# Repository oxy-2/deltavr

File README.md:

# DeltaVR

DeltaVR is a open-source headset with its own controllers made for pcvr, with smaller optics than normal fresnels, custom pcbs and 2 cameras for slam tracking

### our headset:

### our pcbs:

Being a tiny bit more technical I and after the first hundred hours i did alone my 2 friends worked on making an open-source, lightweight PCVR headset built  to be a step up from the hadesvr headset while being more oriented towards technical users due to the smd components, it uses almost all custom hardware aside from the microcontroller, cameras, lenses, screens and drivers, and like linear rods ig, other than that everything is made by us with customs pcbs, and a almost entirely 3d printable design aside from again the ⌀5mm x 160mm stainless steel linear rods, the overarching goal of deltavr was an advanced opensource VR headset with large ipd accommodation, with inside out SLAM tracking and constellation tracked controllers with actually analog triggers on our custom controllers, all under 500 if you have the tools (we got all the way down to 390 actually!)

Oh also in the repo if you wanna see like logs we wrote for every week of the project while in thirdspace then check the /obsidianfiles/ directory, it has all the week folders and hopefully lol well written logs made by all of us with no AI for writing cuz its a tool and that would be stinky.

Also heres the Youtube video we made abt the project <3
https://youtu.be/ISufVPaX-EE

---

## Table of Contents

- [Features](##features)
    
- [Hardware Overview](##hardware-overview)
    
    - [Headset](###headset)
        
    - [Controllers](###controllers)
        
    - [Optics](###optics)
        
    - [Communication](###communication)
        
    - [PCBs](###PCBs)
        
- [Design Decisions](##design-decisions)
	
	- [Cameras](###Cameras)
		
	- [Wireless Communication](###Communication-Wireless)
	    
	- [Optical System](###Optical-System)
		
	- [Mechanical Design](###Mechanical-Design)
	    
- [Firmware](##firmware)
    
- [Assembly](##assembly)
    
- [Bill of Materials](##bill-of-materials)
    
- [Development Status](##development-status)
    
- [Known Issues](##known-issues)
    
- [Project Links](##project-links)
    
- [Credits](##credits)
    
- [License](##license)

---

## Features

- 2x OV9281 global shutter cameras at 120 fps, combined by a usb hub with the hmd pcb all into one 3.2 gen 2 cable to your pc

- custom hmd pcb, mostly smd (hence the technical users bit)

- pseudo pancake optics with 2x fresnels per eye giving better dimensions for just 20 euros for all 4 of the lenses

- a big ipd range, accommodating for all possible human ipd ranges that aren't legit 1 in a trillion

- made to be printed with asa from my own modified ender 3 so like hopefully anyone can print as long as u have an enclosure for the printer, the cushions also are just tpu-lw

- steamvr pcvr compatible

- custom controllers as a part of the project unlike other projects with 3rd party controllers

- high quality imus and mcus, LSM6DSV16Xs and nRF52840s respectively

- tmr joysticks so they never drift and use less battery

- 2 hall effect triggers with an actual analog range for inputs 

- ir constellation tracked controllers

- NRF24L01 on nordic's esb protocol for good range and battery also u.fl support if you want

- under 500 euros if you own the tools, we got all the way down to 390 euros

> *note: deltavr is still and will for a while still be in development, some of these features aren't ready but all listed are being worked on, also in the future there could be more features.

---

## Hardware-Overview

DeltaVR is a custom designed headset with a pair of also custom controllers, its a combination of commercially available components with custom pcbs and mostly 3d printed mechanical parts.

---
### Headset

The headset uses 2x OV9281 global shutter cameras at 120fps for SLAM tracking and tracking.

The cameras and main hmd pcb all connect back to the headset over a usb 3.2 gen 2 hub or if u want ig u can connect them just by 3 cables.

Each of the controllers and the headset pcb have have their own LSM6DSV16X imu and a nRF24L01 gt-24 smd radio module.

The mechanical design is mainly 3d printed with the exception of 2 5mm stainless steel linear rods, other than that its all asa or for cushions and some flexible parts tpu-lw.

---
### Controllers

The DeltaVR controllers use custom designed PCBs and 3d printed enclosures and parts.

The controllers are designed around the nRF52840 based microcontrollers (nRF52840 pro micro) and the LSM6DSV family of imus, for us we used the LSM6DSV16X specifically in the qfn package.

The inputs for the controllers are:
- a tmr joystick
- 2 hall effect sensors for triggers
- 3 buttons, 2 as A,B or X,Y and one for system
- imu inertial tracking
- led constellation tracking
- wireless communication via nRF ESB

> *The tmr sticks and hall effect triggers are there to provide reliable analog input while not dealing with the issues of traditional potentiometer based triggers and sticks like stick drift and wear.

---

### Optics

DeltaVR uses a pair of pseudo pancake lenses, while they have issues and aren't perfect, they allow us to offer optics that take a lot less space than a traditional fresnel lens while still providing good visual quality and only costing the price of 2 pairs of fresnels.

The main reason above all others we went for pseudo pancakes was to have a cheap and also compact optical system, because making a lighter headset means longer sessions are more comfortable, we cant make a bigscreen beyond but something to be maybe similar to a quest 3 was our goal.

---

### Communication

Since only the headset's pcb is wired into the pc that means that the controllers need to communicate with the hmd's pcb and tell it where they are according to the imus along with data about user inputs, the syncing of the led flashes with the cameras on the headset and other stuff like battery data, so we wouldn't want to have wires to the controllers so we have them wireless and they use the nRF ESB (Enhanced Shock-Burst) protocol to communicate with the headset efficiently and in a way that doesnt drain too much battery.

---

### PCBs

After i figured out how i wanted to make the headset as a rough sketch in my mind and then on paper i started with the PCBs, i wanted the controller boards when assembled and in use not to drain much battery because that would allow for long play sessions which was a personal gripe i had with the rechargeable batteries i have for my Quest 3's controllers.

So for the PCBs the main thing you choose and that id talk abt here would be what they look like and what components they use, so starting with the controllers they use a mosfet which is wired to the mcu which then gets pulsed rapidly to be able to feed the leds their peak power for a fraction of a second before they turn back off and then on again, basically strobing very fast, the mosfet i chose was a IRLZ44N, the leds were just simple 5mm emitters, the imu i chose was because i made slime trackers before this headset and for slimevr the imu i used in my trackers was a LSM6DSR and it was a great imu so i decided for this to step up to using LSM6DSV16Xs, the choice of sticks and triggers was simple cuz i wanted to have efficient ones that don't wear out, SS49Es are cheap and so is the ginful tmr ps5 replacement stick so i went with those, the last thing is the radio module, the nRF24L01 in the form of the gt-24 smd board, its small, have a antenna plug if u wanna use it and also works well and is cheap, so that was a no brainer.

For the hmd pcb all the choices were the same as for the controllers, just theres a rgb led for status and like no battery.

here are the schematics:

---

## Design-Decisions

A run down of all the reasons of the things that were picked and why they were, etc.

---

### Cameras

The OV9281 cameras i chose for this project, namely they have a tiny sensor, the issue with this is finding proper lenses for them is quite the endeavor so the thing is, you can actually just get this camera with great lenses but you'll only find lenses above 90º on ones that output MIPI for some reason, its prolly because of the factories in which they are made but yeah, so now there's an issue either search forever to find the right lens at a good price, spend a fortune on the right lens or figure out how to get your MIPI back to like usb using something like a raspberry pi cm5 or sum.

So what did we do, we found the right lens at a very good price, with one caveat, one small caveat, unless i have it shipped through to a friend and then from the friend to me it will cost hundreds of euros to ship, so that's what we are doing, so we get easy to connect usb cameras with good lenses, all i had to do was a couple write ups on logistics.

---

### Wireless-Communication

So like if you're in the know with slimevr you'll understand all this but basically something like an esp32 works over wifi which is good and it works well don't get me wrong but its first and foremost very draining on battery, or at least it is in comparison to what we are using, that being ESB, so basically for controllers you wouldn't want them to run out of battery fast so like ESB is perfect, ESB stands for Enhanced Shock-Burst it's a *sadly* proprietary protocol developed by Nordic for use with their wireless microcontrollers and devices, a basic explanation of what it does would be is that its a 2.4 GHz communication protocol that differs from things like Bluetooth because it has absolutely NO native security and its interference handling is pretty basic, which those two things are both sum Bluetooth does very well, anyways so now the upsides of ESB for us are massive because the latency is like actually non-existent with ESB and along with that the power consumption is so low that for example my nRF52840 pro micro based smolslime vr trackers still turn on even though i charged them literally like multiple months ago, though tbf i don't use them often, but basically they are very efficient is what I'm trying to say.

---

### Optical-System

I will keep this one short because it's rather big as a actual topic, but basically real pancake lenses are INCREDIBLY INCREDIBLY expensive, especially custom made ones, although high quality PMMA fresnel lenses are very cheap and can well just be cut up as long as you do it right, so basically if you have a standard fresnel like in the quest 2 for example, in the quest 2 there is just one thick fresnel and its rather far from the screen due to the nature of fresnels, so the result is a thicker headset because a normal fresnel needs more space to be able to work with the light, now our solution is pancake lenses, a very smart trick with fresnels first seen made by a guy named WalkerDev, check out the article [here](https://hackaday.io/project/187343-the-psuedopancakes), anyways so basically by stacking two fresnels the ability for them to bend light is far far stronger and hence they can be far far closer to the display meaning you get a way smaller headset, although they do have caveats and aren't perfect neither are they as good as actual pancake lenses, the issue with them is they can split light slightly at the edges meaning they can produce chromatic aberration or god rays, and if the alignment isn't done well its quite bad, however in my opinion it works well and is a good tradeoff to make for what you get back.

---

### Mechanical-Design

Last up is the mechanical design, mechanically this headset is pretty simple, we have the displays mounted on linear rods with a tiny bit of grease and then the display mounts have a rack and a pinion is between the racks and connects to a lil thing on the outside though u can just adjust them by moving one display thing inward or outward, the other will do the same cuz they are connected with the racks and pinion, then other than that is the head strap and the adjustable part for it, the adjustable part is again just a rack and pinion system with a big thing on the outside to turn easily and then the head strap needs its flexible parts and cushions which are done with the wonderful TPU-LW filament that eSUN makes which is TPU but its got sum stuff inside it that make it like make tiny tiny bubbles under high heat so like by modulating the nozzle temp on my printer i can get softer and more expanded / bigger parts with higher temps and get normal hard TPU with lower temps, great stuff honestly just look out for clogs.

---

## Firmware

So firmware, we are actively working on is as I'm writing this, its just very hard, we have decided to use renode, renode is amazing but we aren't very good at using it or we are still learning lol, anyways also we are using the Visual System Designer too which is sum i set up but it has like absolutely ZERO documentation as far as i have seen.

---

## Assembly

You'll need some nuts and m3 screws and then, well we don't actually have like the headset in person or built yet so its hard to say but basically you'd print all the parts and then fit the display gantry things in and put the rods in and through them then secure the rods in with the rod end stops, then put on the camera mounts and then put the cameras in and screen them into place, then just place the display driver board on the top flat spot on the head strap and screen it in with heat set inserts or like me just heat the screws and shove em in, then lastly put the splitter in at the top inside of the headset shell and plug the displays and driver boards in, then put the usb hub on top and plug everything in and have the hdmi from the driver board and usb 3.2 gen 2 cable from the hub go back to your pc and plug em in and your ready to go!

---

## Bill-of-Materials

check out the BoM folder in the root of the repo.

---

## Development-Status

rn we are working on well i was working on this readme, and we just need to buy and build the headset but before that we are done our controllers, so with v2.0.0 released all we need done is the phyiscal build and like the software and firmware once we have the prototype 

---

## Known-Issues

uhh not many, we try to fix the issues yk, but uh like we got some issues with vsd and renode rn thats abt it tho

---

## Project-Links

You can check me, oxy-2 out on my site at [oxygenated.uk]( https://www.oxygenated.uk) and you can check out my friend grand at [nesaule.dev](https://nesaule.dev) and you can see the work i did with stardance [here](https://stardance.hackclub.com/projects/26318) and lastly heres our repo on github, [deltavr](https://github.com/oxy-2/deltavr) 

---

## Credits

This project was made firstly by me oxy-2 and also my 2 friends helped out for the thirdspace program, so big thanks to grand and john!

This project was inspired by the Quest 3 made by Meta, the Bigscreen Beyond and HadesVR also a couple other small things i can't really remember, we wrote most our code ourselves and modeled everything ourselves according to the design i made so its not stolen.

Other than that we used tools like renode, blender, onshape and kicad along side very common programming languages like C, C++, Python and C#.

And lastly but certainly not least a MASSIVE thanks to [Hack Club](https://hackclub.com/) they really are what let me make this project, with the rewards for the programs I've worked with motivating me to work on this as my dream project and in general they are a very awesome bunch of people and ill always be thankful to have had worked with them <3

---

## License

#### Legal Notice

Copyright (c) 2026 oxy-2 and the DeltaVR Project Contributors.

This repository is distributed under a split-licensing model. All custom software, tracking scripts, and firmware components are licensed under the GNU General Public License v3.0 (GPL-3.0). All custom schematic diagrams, KiCad layouts, 3D printable enclosures, and hardware manufacturing files are licensed under the CERN Open Hardware Licence Version 2 - Strongly Reciprocal (CERN-OHL-S v2). Handwritten engineering documentation and Obsidian notes are licensed under Creative Commons Attribution-ShareAlike 4.0 International (CC BY-SA 4.0).

This project is provided "as is" without warranty of any kind, express or implied. For full path breakdowns and legal terms, see the root LICENSE file.

---

made with love.
by oxy

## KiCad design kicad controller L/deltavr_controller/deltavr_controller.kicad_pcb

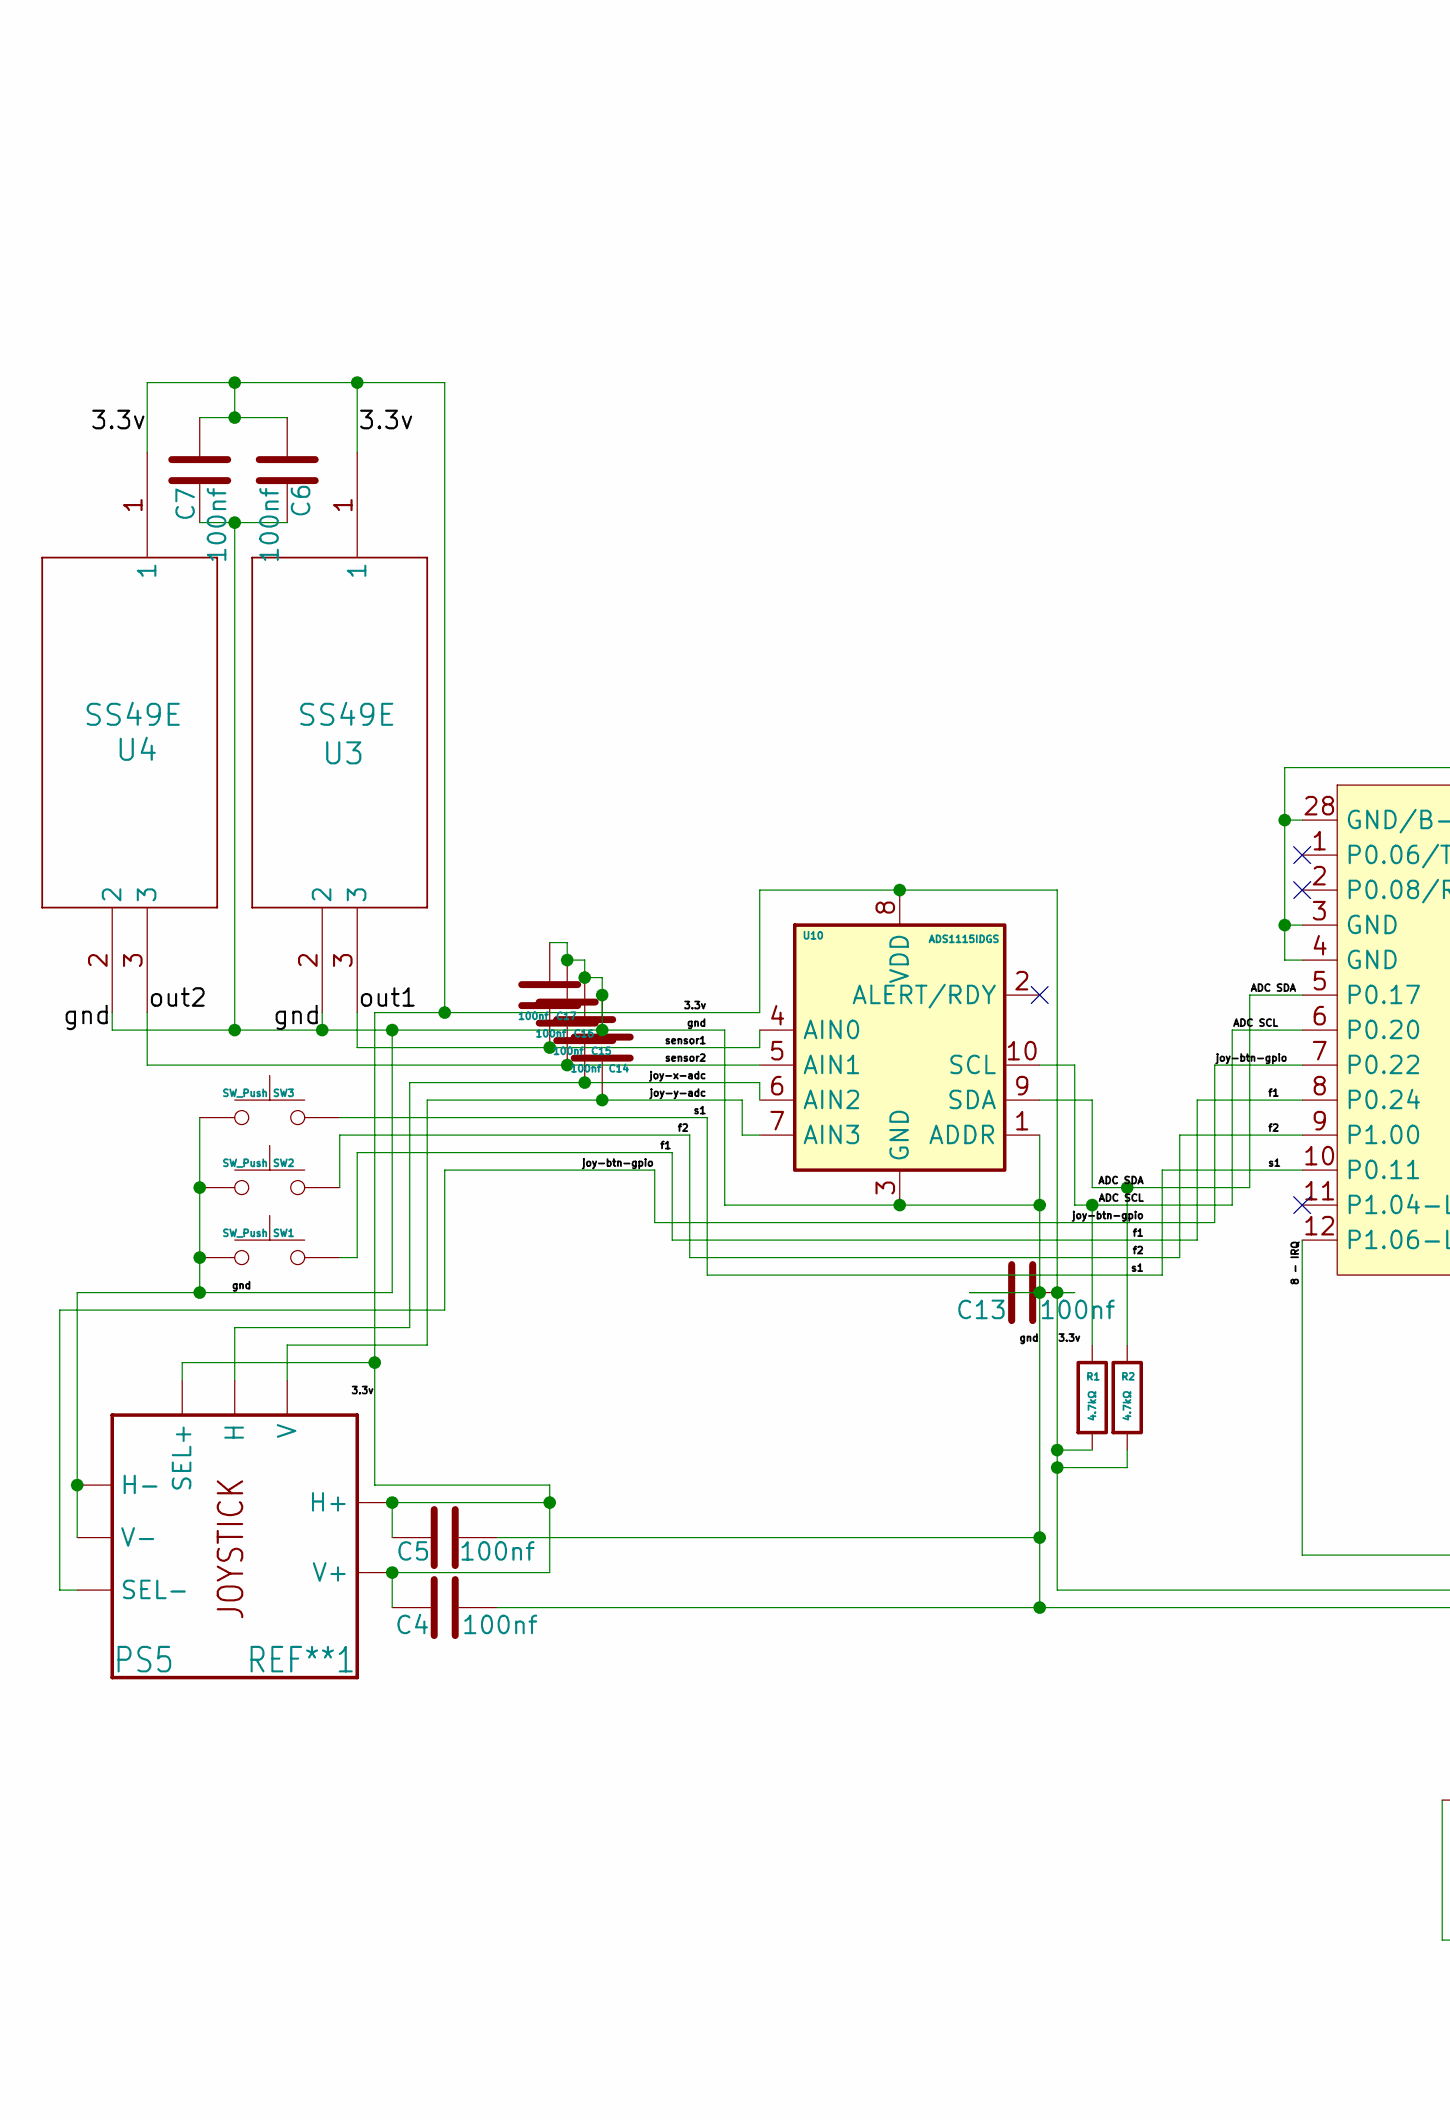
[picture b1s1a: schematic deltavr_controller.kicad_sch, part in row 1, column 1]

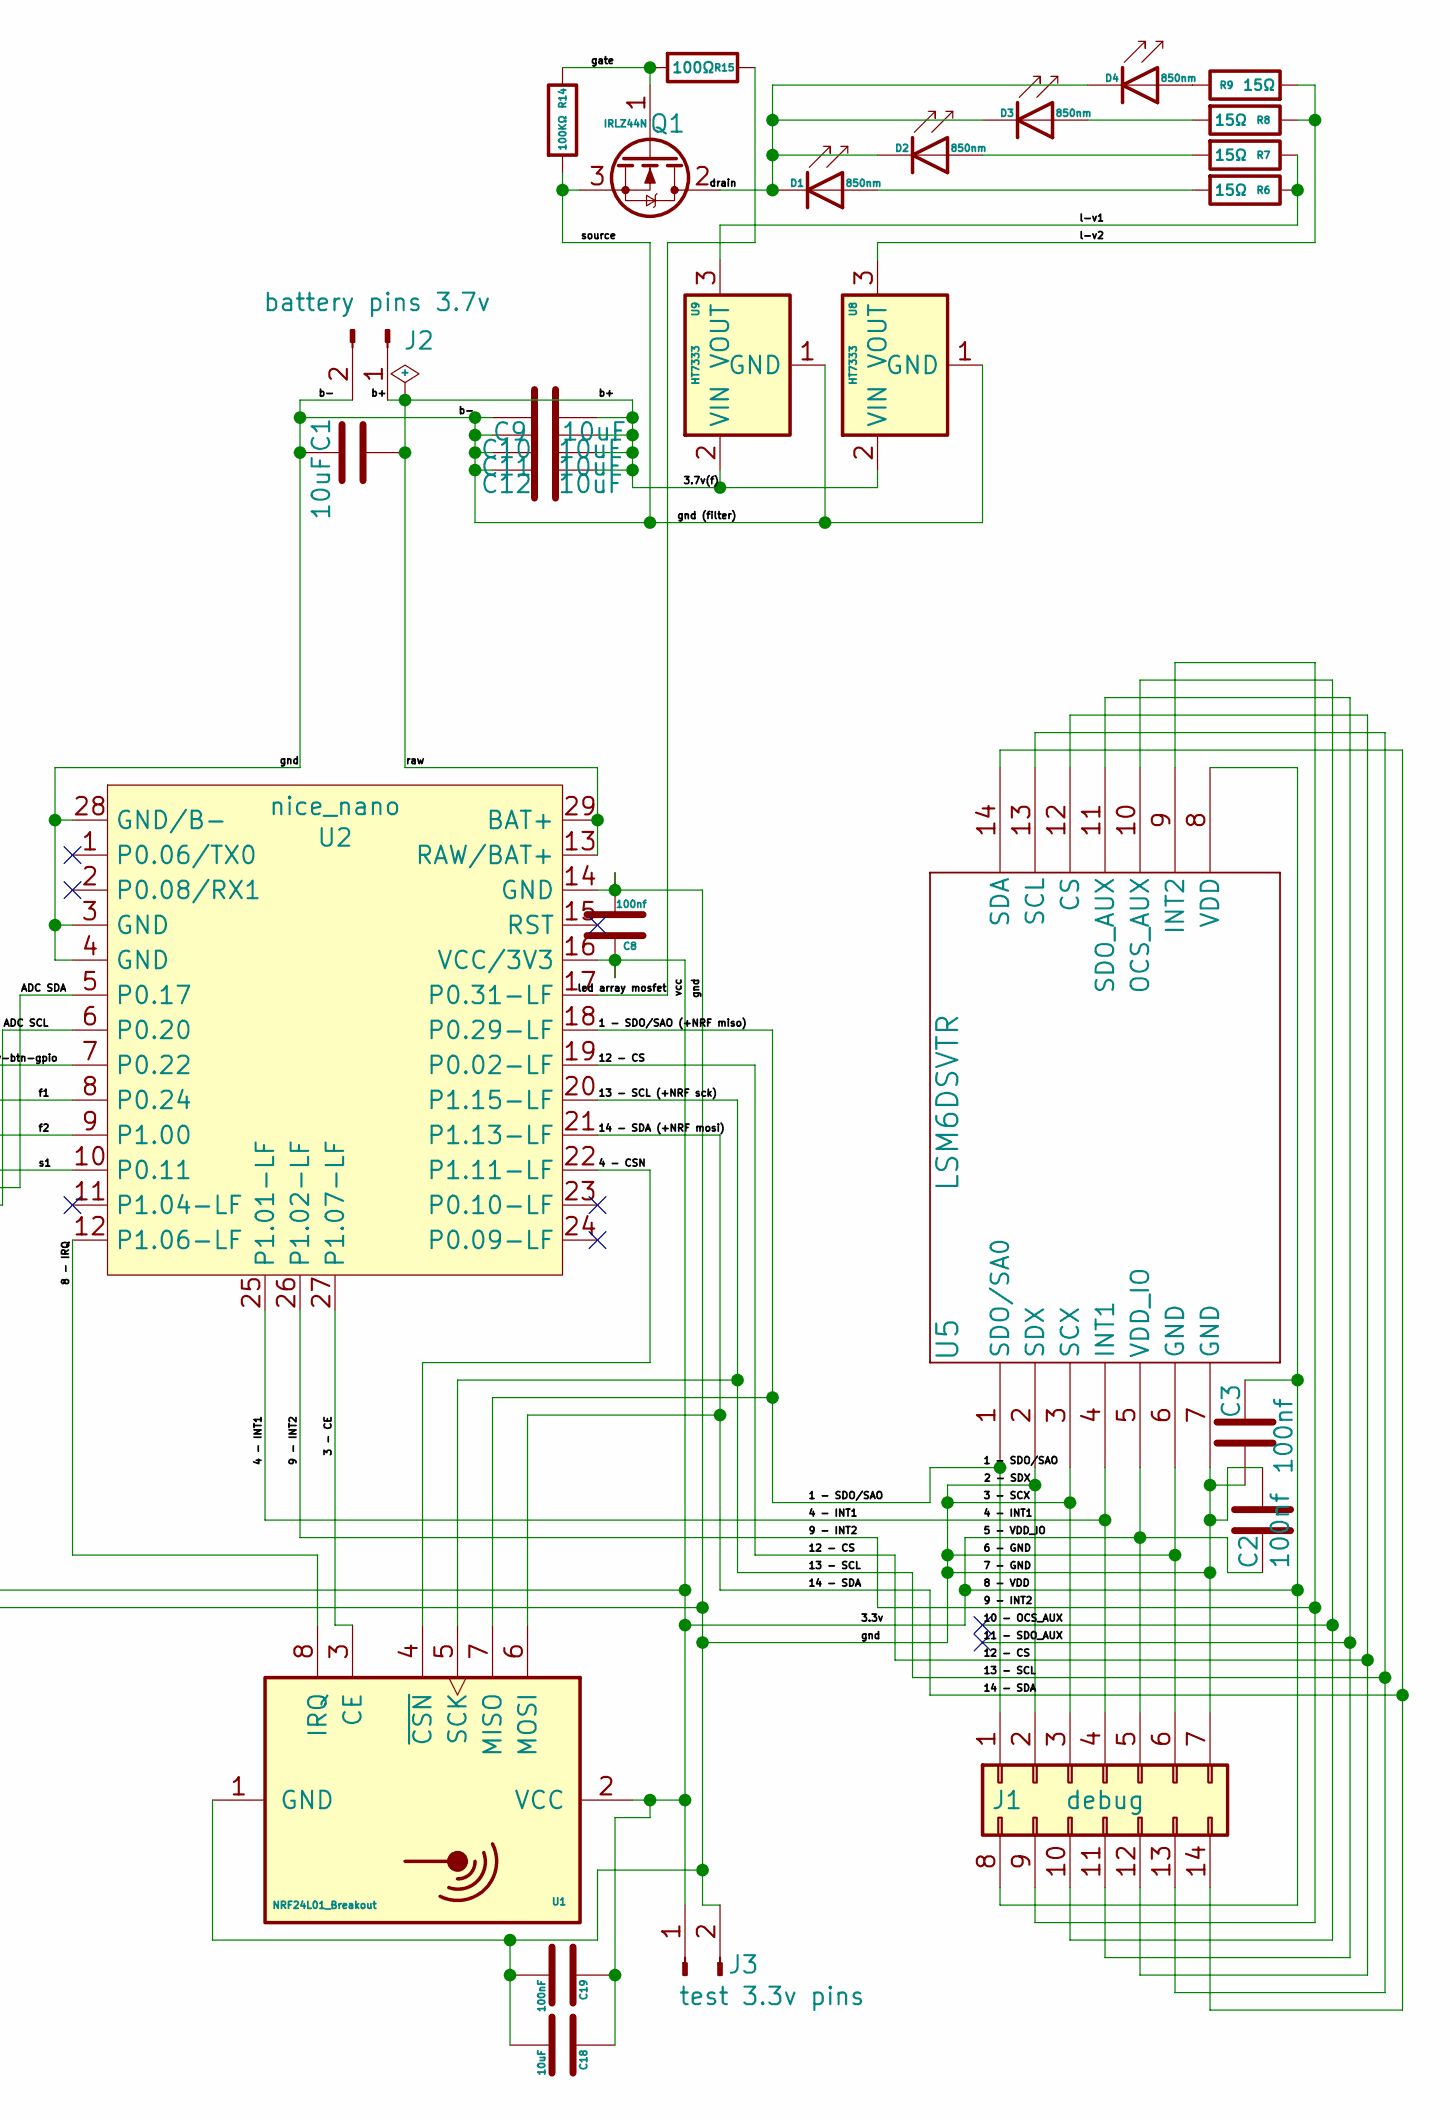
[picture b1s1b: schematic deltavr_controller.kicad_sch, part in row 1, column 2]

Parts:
C1, C9, C10, C11, C12, C18: 10uF; C_0603_1608Metric_Pad1.08x0.95mm_HandSolder
C2, C3, C4, C5, C6, C7, C8, C13, C14, C15, C16, C17: 100nf; C_0603_1608Metric_Pad1.08x0.95mm_HandSolder
C19: 100nF; C_0603_1608Metric_Pad1.08x0.95mm_HandSolder
D1, D2, D3, D4: 850nm; LED_D5.0mm_IRGrey
J1: debug; PinSocket_2x07_P2.54mm_Vertical
J2: battery pins 3.7v; PinSocket_1x02_P2.54mm_Vertical
J3: test 3.3v pins; PinSocket_1x02_P2.54mm_Vertical
Q1: IRLZ44N; TO-220-3_Vertical
R1, R2: 4.7kΩ; R_0603_1608Metric_Pad0.98x0.95mm_HandSolder
R6, R7, R8, R9: 15Ω; R_0603_1608Metric_Pad0.98x0.95mm_HandSolder
R14: 100KΩ; R_0603_1608Metric_Pad0.98x0.95mm_HandSolder
R15: 100Ω; R_0603_1608Metric_Pad0.98x0.95mm_HandSolder
REF**1: PS5; Joystick
SW1, SW2, SW3: SW_Push; SW_PUSH_6mm_H4.3mm
U1: NRF24L01_Breakout; nRF24L01_Breakout
U2: nice_nano; nice_nano_AH_Reversible
U3, U4: SS49E; SEN3_SS49E_HNW
U5: LSM6DSVTR; LGA14-L_2P59X3P1X0P5_STM
U8, U9: HT7333; SOT-89-3
U10: ADS1115IDGS; TSSOP-10_3x3mm_P0.5mm

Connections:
/1 - SDO/SAO: J1.1, U1.7 (MISO), U2.18 (P0.29-LF), U5.1 (SDO/SA0)
/2 - SDX: C1.1, C2.2, C3.1, C4.2, C5.2, C6.2, C7.2, C8.1, C9.1, C10.1, C11.1, C12.1, C13.1, C14.2, C15.2, C16.2, C17.2, C18.2, C19.2, J1.2, J1.3, J1.6, J1.7, J2.2, J3.2, Q1.3 (S), R14.2, REF**1.1 (H-), REF**1.1' (V-), SW1.1, SW2.1, SW3.1, U1.1 (GND), U2.3 (GND), U2.4 (GND), U2.14 (GND), U2.28 (GND/B-), U3.2, U4.2, U5.2 (SDX), U5.3 (SCX), U5.6 (GND), U5.7 (GND), U8.1 (GND), U9.1 (GND), U10.1 (ADDR), U10.3 (GND)
/3 - CE: U1.3 (CE), U2.27 (P1.07-LF)
/3.3v: C2.1, C3.2, C4.1, C5.1, C6.1, C7.1, C8.2, C13.2, C18.1, C19.1, J1.5, J1.8, J3.1, R1.2, R2.2, REF**1.3 (H+), REF**1.3' (V+), REF**1.a (SEL+), U1.2 (VCC), U2.16 (VCC/3V3), U3.1, U4.1, U5.5 (VDD_IO), U5.8 (VDD), U10.8 (VDD)
/3.7v(f): C1.2, C9.2, C10.2, C11.2, C12.2, J2.1, U2.13 (RAW/BAT+), U2.29 (BAT+), U8.2 (VIN), U9.2 (VIN)
/4 - CSN: U1.4 (~CSN), U2.22 (P1.11-LF)
/4 - INT1: J1.4, U2.25 (P1.01-LF), U5.4 (INT1)
/8 - IRQ: U1.8 (IRQ), U2.12 (P1.06-LF)
/9 - INT2: J1.9, U2.26 (P1.02-LF), U5.9 (INT2)
/10 - OCS_AUX: J1.10, U5.10 (OCS_AUX)
/11 - SDO_AUX: J1.11, U5.11 (SDO_AUX)
/12 - CS: J1.12, U2.19 (P0.02-LF), U5.12 (CS)
/13 - SCL: J1.13, U1.5 (SCK), U2.20 (P1.15-LF), U5.13 (SCL)
/14 - SDA: J1.14, U1.6 (MOSI), U2.21 (P1.13-LF), U5.14 (SDA)
/ADC SCL: R1.1, U2.6 (P0.20), U10.10 (SCL)
/ADC SDA: R2.1, U2.5 (P0.17), U10.9 (SDA)
/drain: D1.1 (K), D2.1 (K), D3.1 (K), D4.1 (K), Q1.2 (D)
/f1: SW1.2, U2.8 (P0.24)
/f2: SW2.2, U2.9 (P1.00)
/gate: Q1.1 (G), R14.1, R15.2
/joy-btn-gpio: REF**1.c (SEL-), U2.7 (P0.22)
/joy-x-adc: C15.1, REF**1.2 (H), U10.6 (AIN2)
/joy-y-adc: C14.1, REF**1.2' (V), U10.7 (AIN3)
/l-v1: R6.1, R7.1, U9.3 (VOUT)
/l-v2: R8.1, R9.2, U8.3 (VOUT)
/led array mosfet: R15.1, U2.17 (P0.31-LF)
/out1: C17.1, U3.3, U10.4 (AIN0)
/out2: C16.1, U4.3, U10.5 (AIN1)
/s1: SW3.2, U2.10 (P0.11)
unnamed: D1.2 (A), R6.2
unnamed: D2.2 (A), R7.2
unnamed: D3.2 (A), R8.2
unnamed: D4.2 (A), R9.1

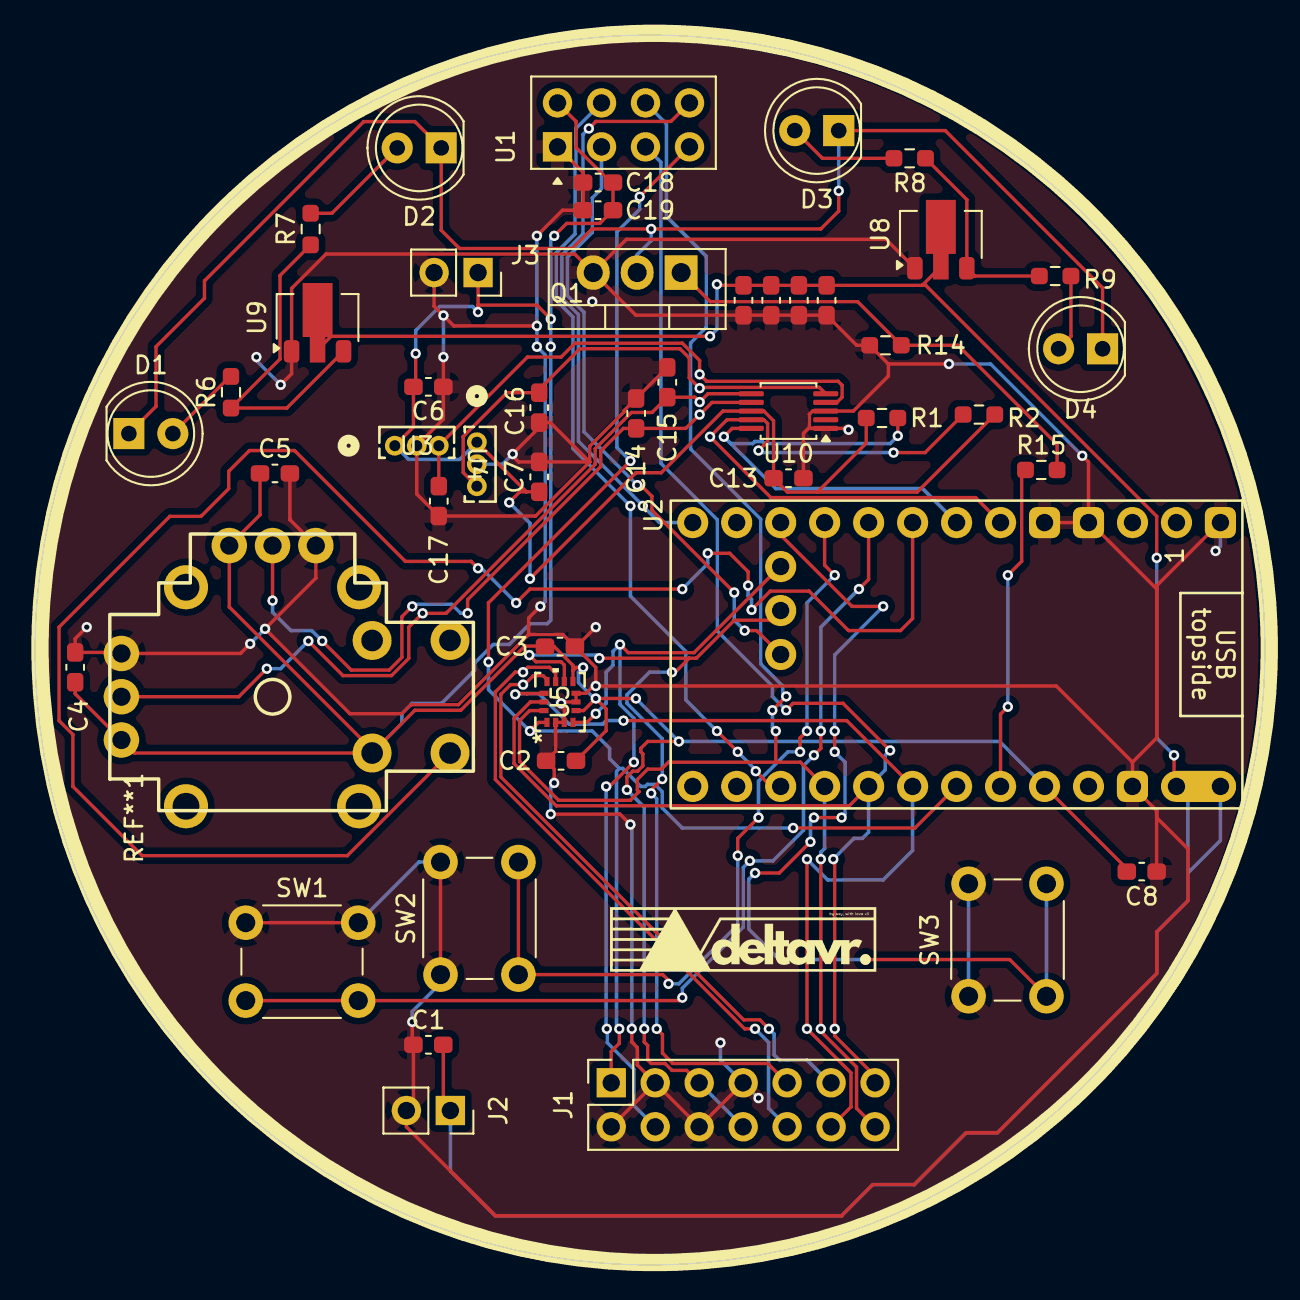
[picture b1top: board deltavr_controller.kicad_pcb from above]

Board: 2 copper layers, 71.0 x 71.0 mm, 46 parts (0 on the bottom side), 32 nets.

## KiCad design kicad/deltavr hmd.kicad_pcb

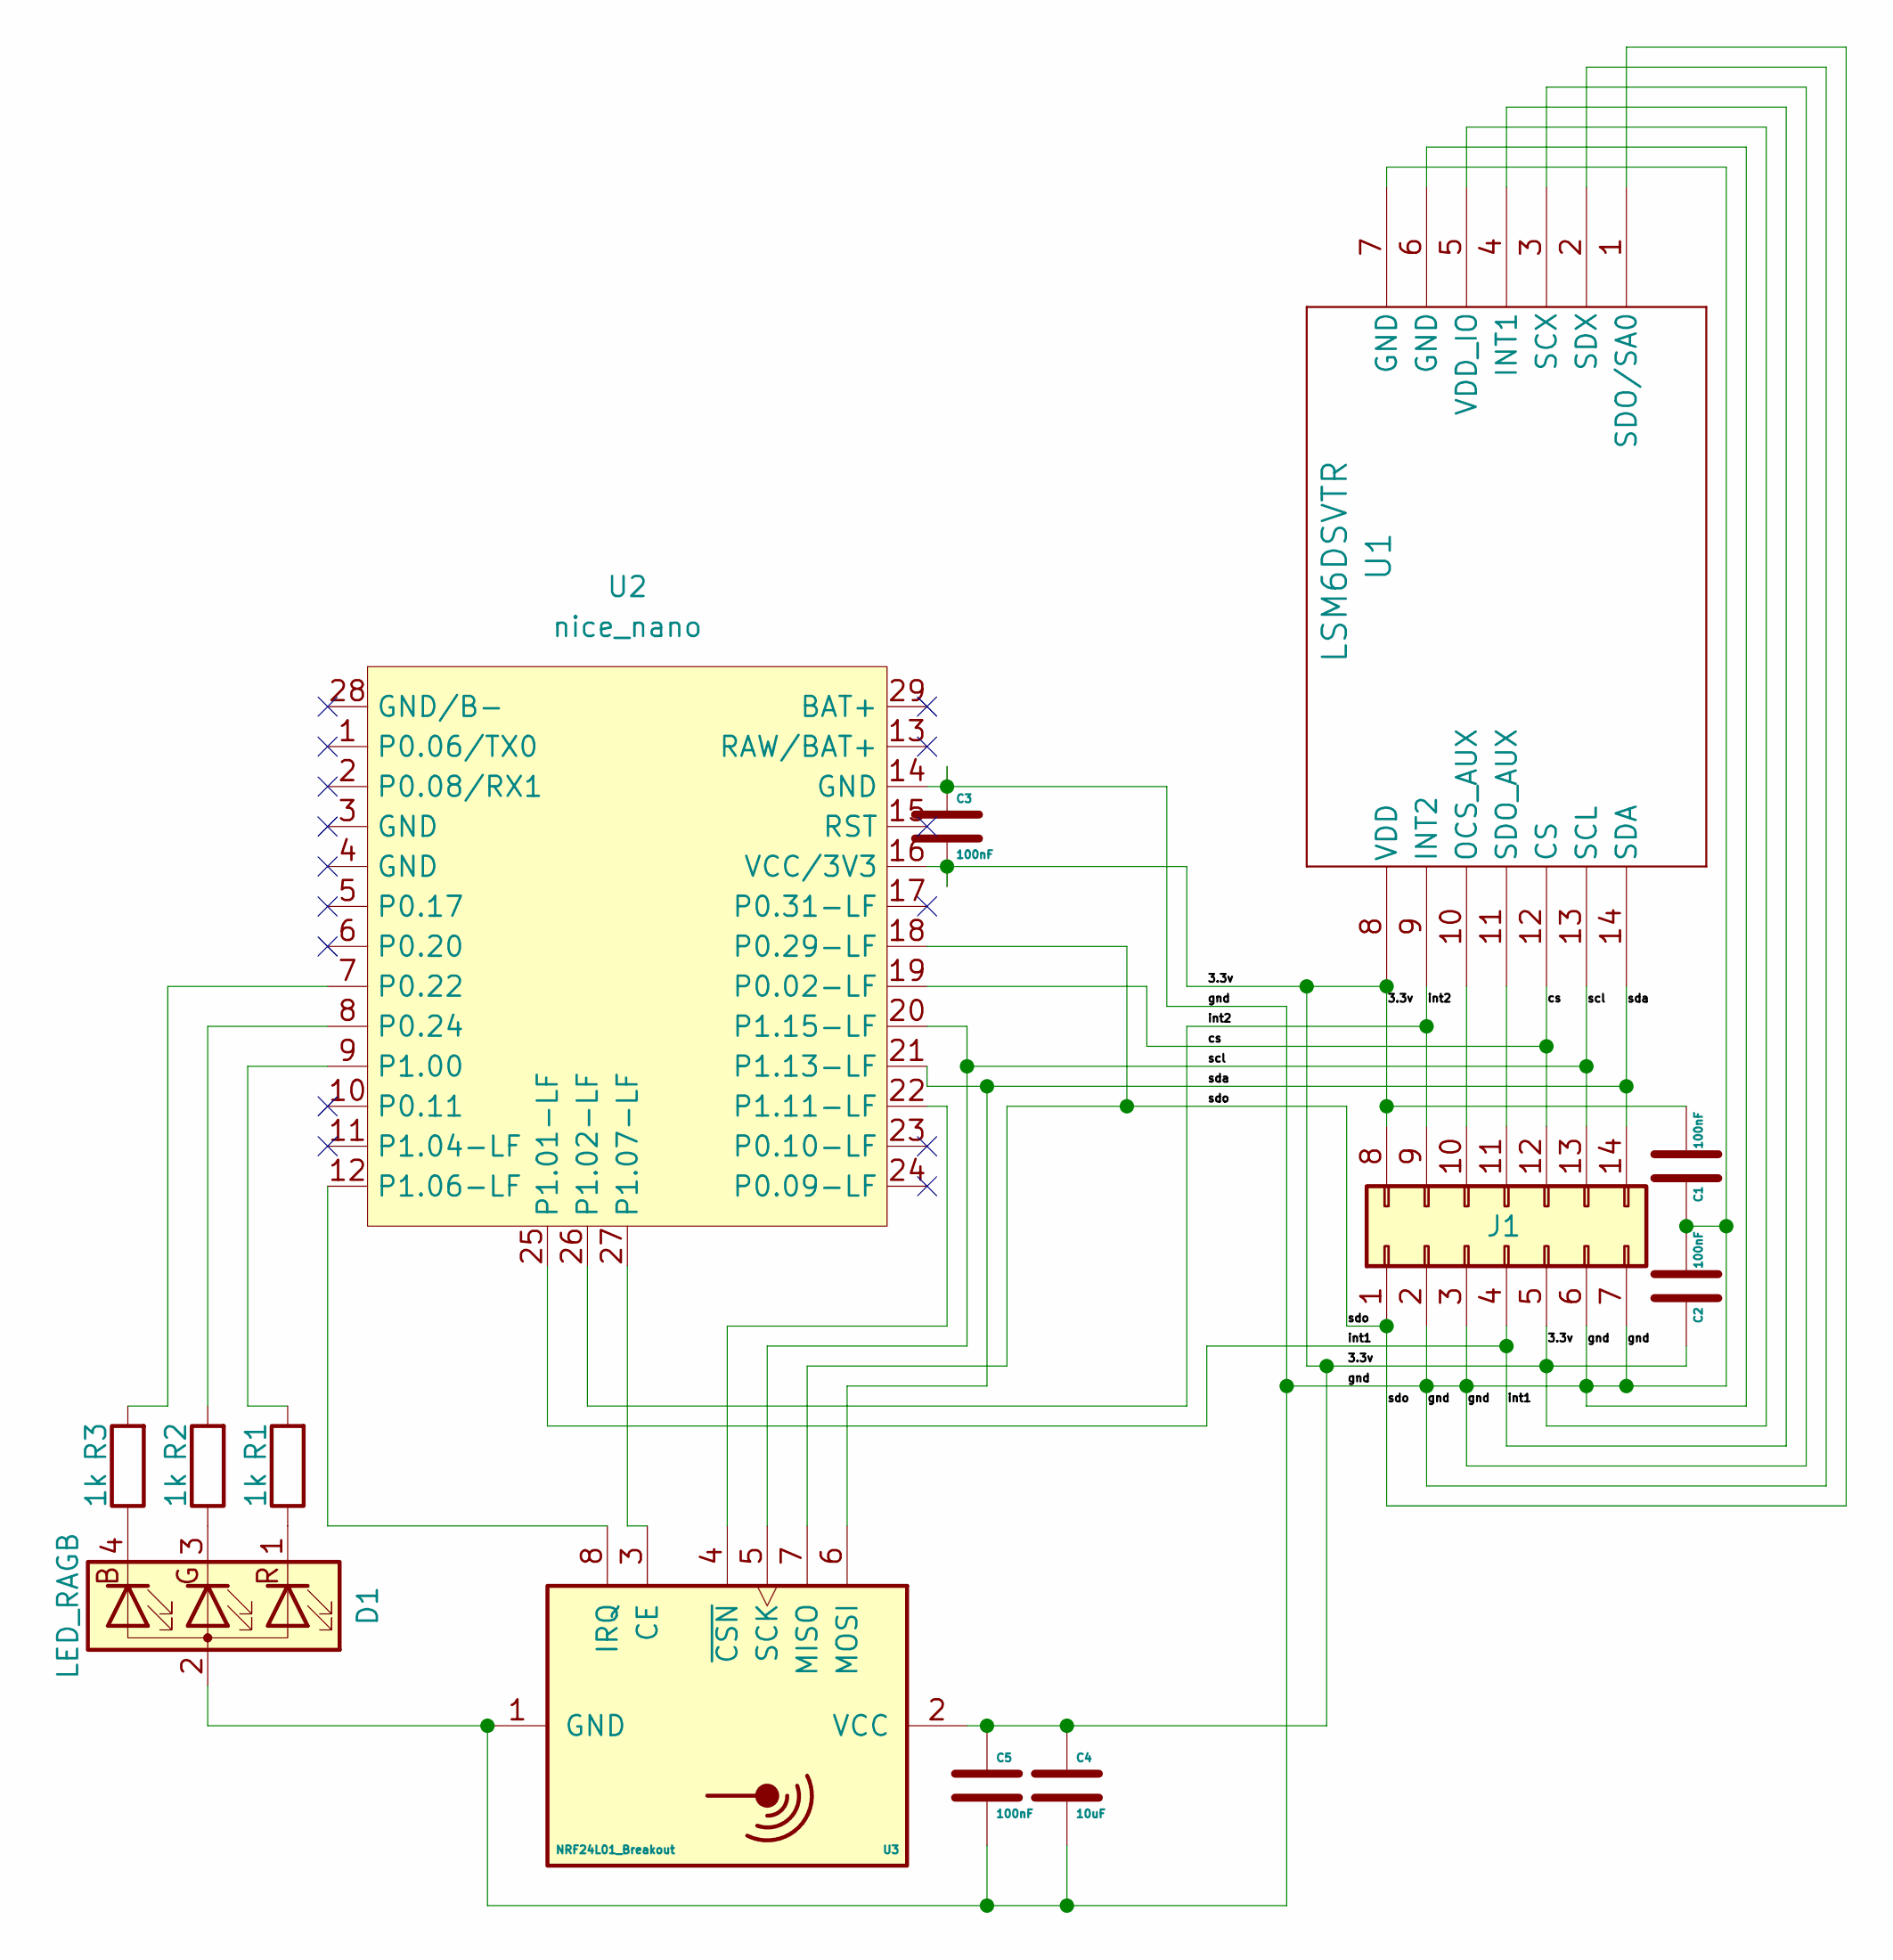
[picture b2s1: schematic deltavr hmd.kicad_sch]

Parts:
C1, C2, C3, C5: 100nF; C_0603_1608Metric_Pad1.08x0.95mm_HandSolder
C4: 10uF; C_0603_1608Metric_Pad1.08x0.95mm_HandSolder
D1: LED_RAGB; LED_D5.0mm-4_RGB_Wide_Pins
J1: Conn_02x07_Top_Bottom; PinHeader_2x07_P2.54mm_Vertical
R1, R2, R3: 1k; R_0603_1608Metric_Pad0.98x0.95mm_HandSolder
U1: LSM6DSVTR; LGA14-L_2P59X3P1X0P5_STM-M
U2: nice_nano; nice_nano_AH_Reversible
U3: NRF24L01_Breakout; nRF24L01_Breakout

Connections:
/3.3v: C1.2, C2.1, C3.1, C4.2, C5.2, J1.5, J1.8, U1.5 (VDD_IO), U1.8 (VDD), U2.16 (VCC/3V3), U3.2 (VCC)
/cs: J1.12, U1.12 (CS), U2.19 (P0.02-LF)
/gnd: C1.1, C2.2, C3.2, C4.1, C5.1, D1.2 (A), J1.2, J1.3, J1.6, J1.7, U1.2 (SDX), U1.3 (SCX), U1.6 (GND), U1.7 (GND), U2.14 (GND), U3.1 (GND)
/int1: J1.4, U1.4 (INT1), U2.25 (P1.01-LF)
/int2: J1.9, U1.9 (INT2), U2.26 (P1.02-LF)
/scl: J1.13, U1.13 (SCL), U2.20 (P1.15-LF), U3.5 (SCK)
/sda: J1.14, U1.14 (SDA), U2.21 (P1.13-LF), U3.6 (MOSI)
/sdo: J1.1, U1.1 (SDO/SA0), U2.18 (P0.29-LF), U3.7 (MISO)
unnamed: D1.4 (BK), R3.1
unnamed: D1.3 (GK), R2.1
unnamed: D1.1 (RK), R1.1
unnamed: J1.10, U1.10 (OCS_AUX)
unnamed: J1.11, U1.11 (SDO_AUX)
unnamed: R3.2, U2.7 (P0.22)
unnamed: R2.2, U2.8 (P0.24)
unnamed: R1.2, U2.9 (P1.00)
unnamed: U2.12 (P1.06-LF), U3.8 (IRQ)
unnamed: U2.27 (P1.07-LF), U3.3 (CE)
unnamed: U2.22 (P1.11-LF), U3.4 (~CSN)

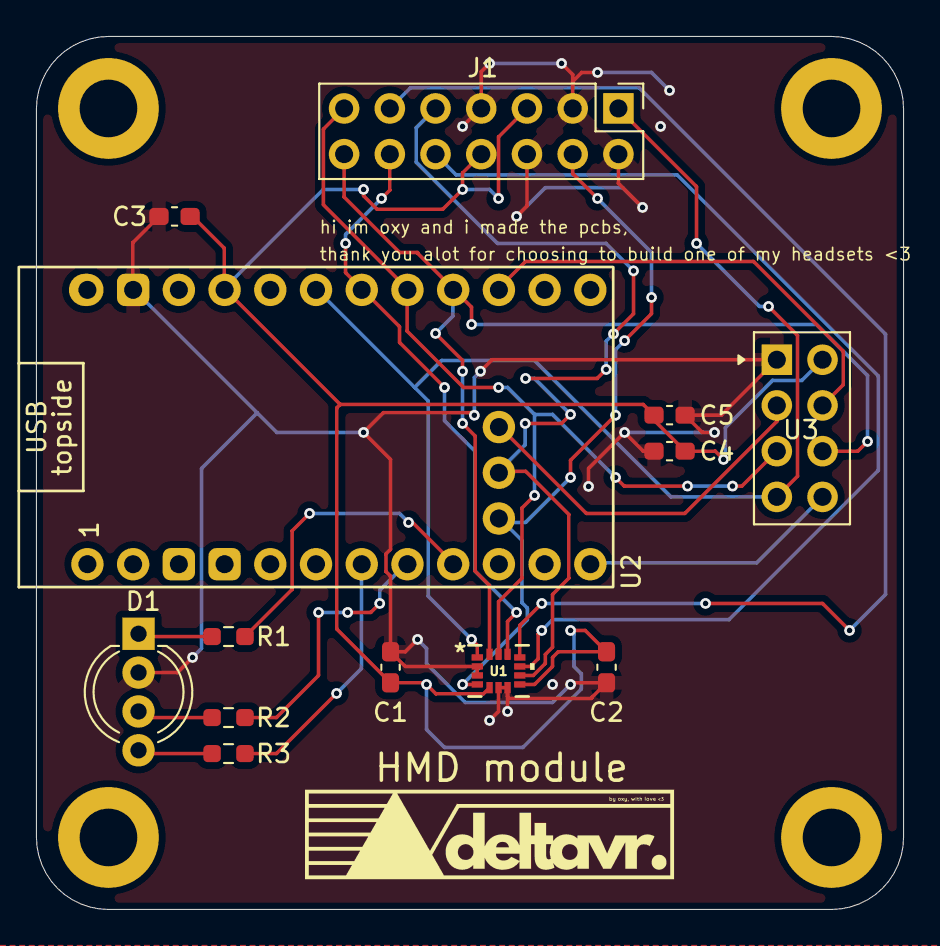
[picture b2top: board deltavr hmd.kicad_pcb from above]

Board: 2 copper layers, 48.2 x 48.5 mm, 17 parts (0 on the bottom side), 19 nets.

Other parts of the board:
M3 screw, M3 screw#2, M3 screw#3, M3 screw#4: MountingHole_3.2mm_M3_DIN965_Pad

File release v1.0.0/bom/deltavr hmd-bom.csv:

"Reference","Value","Footprint"
"C1","100nF","Capacitor_SMD:C_0603_1608Metric_Pad1.08x0.95mm_HandSolder"
"C2","100nF","Capacitor_SMD:C_0603_1608Metric_Pad1.08x0.95mm_HandSolder"
"C3","100nF","Capacitor_SMD:C_0603_1608Metric_Pad1.08x0.95mm_HandSolder"
"C4","10uF","Capacitor_SMD:C_0603_1608Metric_Pad1.08x0.95mm_HandSolder"
"C5","100nF","Capacitor_SMD:C_0603_1608Metric_Pad1.08x0.95mm_HandSolder"
"D1","LED_RAGB","LED_THT:LED_D5.0mm-4_RGB_Wide_Pins"
"J1","Conn_02x07_Top_Bottom","Connector_PinHeader_2.54mm:PinHeader_2x07_P2.54mm_Vertical"
"R1","1k","Resistor_SMD:R_0603_1608Metric_Pad0.98x0.95mm_HandSolder"
"R2","1k","Resistor_SMD:R_0603_1608Metric_Pad0.98x0.95mm_HandSolder"
"R3","1k","Resistor_SMD:R_0603_1608Metric_Pad0.98x0.95mm_HandSolder"
"U1","LSM6DSVTR","footprints:LGA14-L_2P59X3P1X0P5_STM-M"
"U2","nice_nano","nicenano footprint:nice_nano"
"U3","NRF24L01_Breakout","RF_Module:nRF24L01_Breakout"
